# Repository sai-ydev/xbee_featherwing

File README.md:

# xbee_featherwing
XBee Featherwing

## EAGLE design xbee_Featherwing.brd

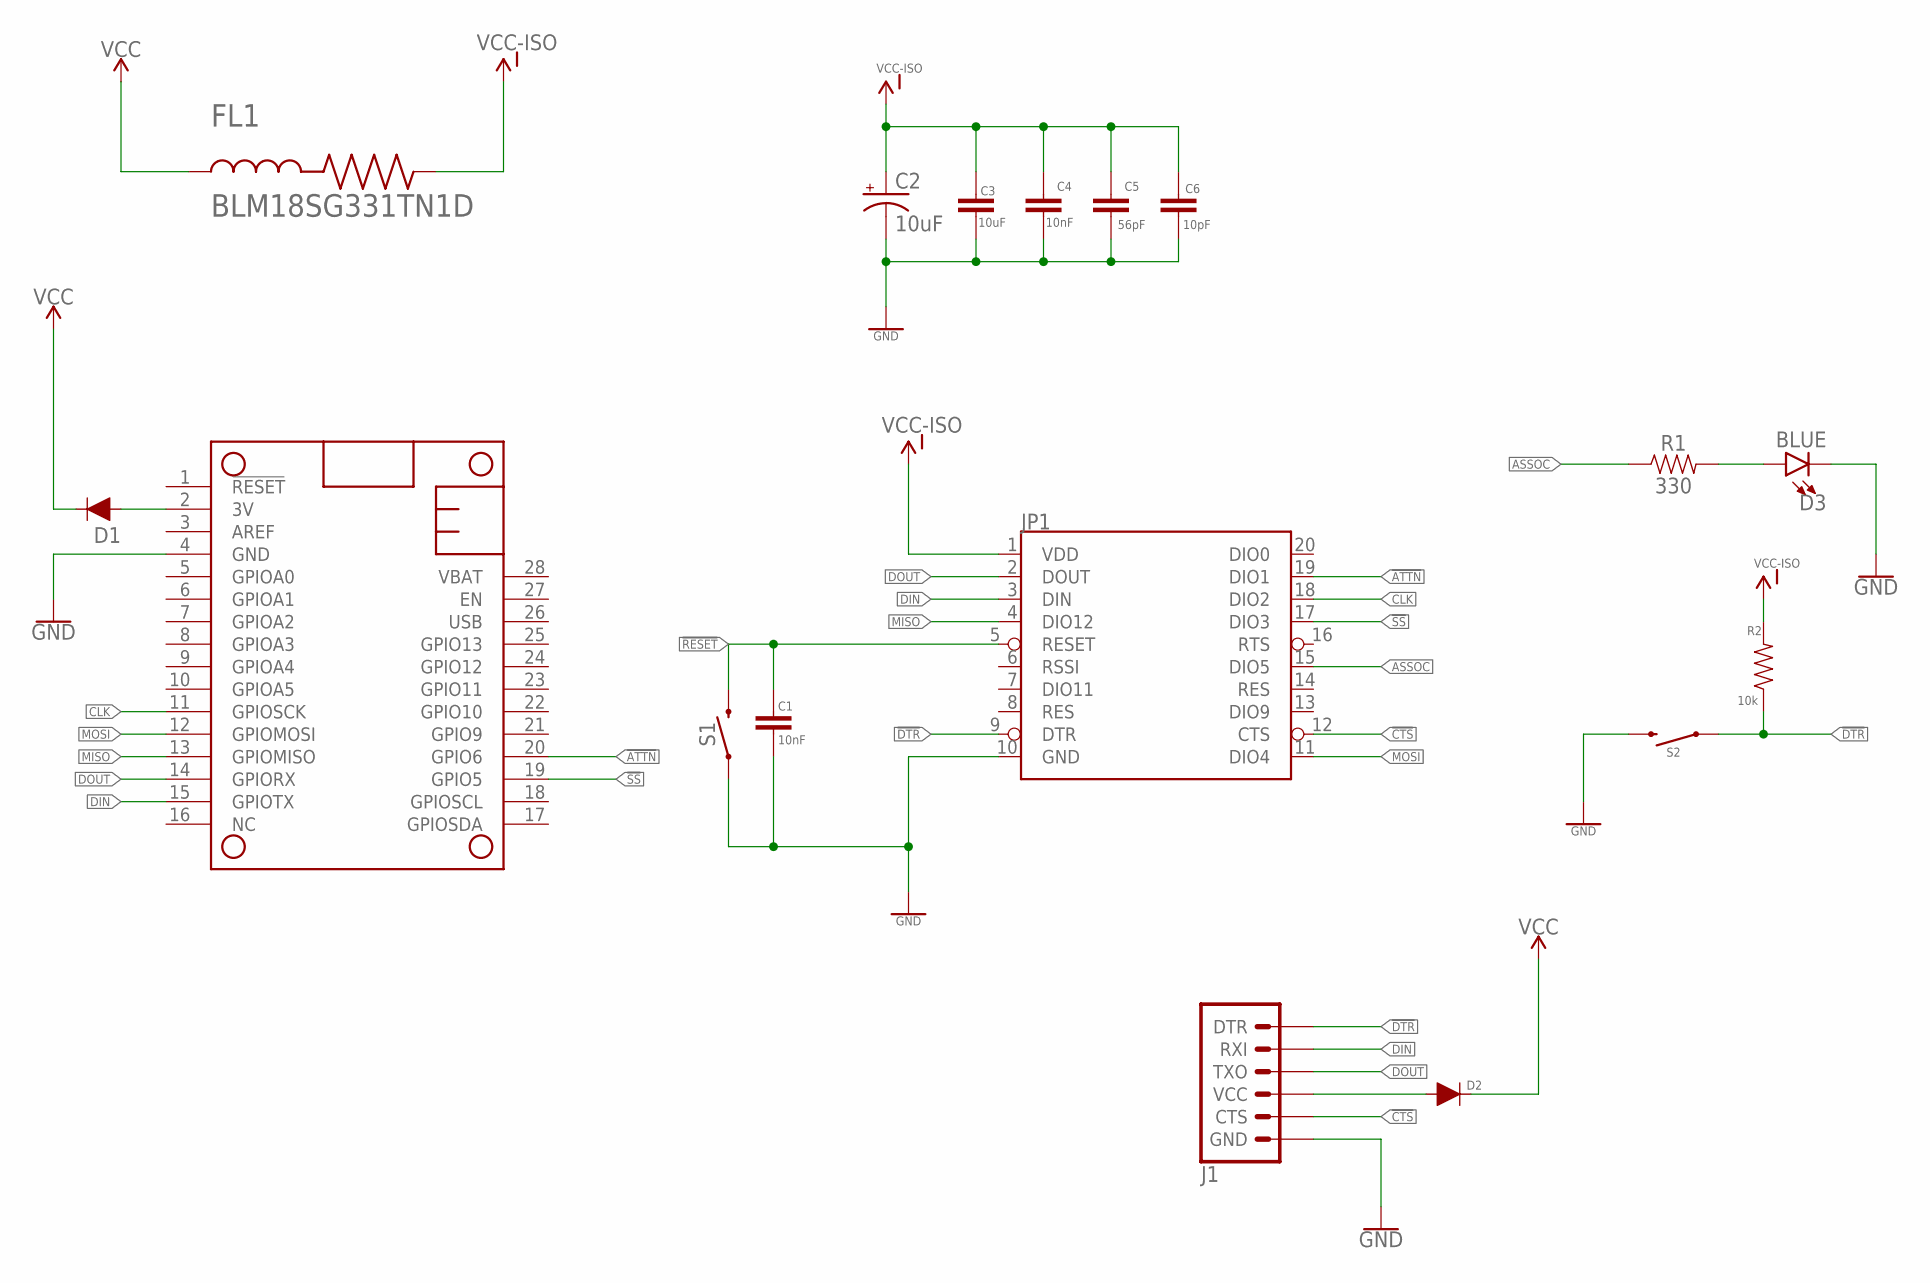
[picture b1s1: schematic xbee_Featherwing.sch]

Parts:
C1, C4: 10nF; 0603
C2: 10uF; EIA3216
C3: 10uF; 0603
C5: 56pF; 0603
C6: 10pF; 0603
D1, D2: 250mA/100V; SOD-323
D3: BLUE; LED-0603
FL1: BLM18SG331TN1D; BEADC1608X65N
J1: 6_PIN_SERIAL_TARGETSILK; 6_PIN_SERIAL_TARGET_SIDE_W_SILK
JP1: XBEESMD; XBEE-SMD
MS1: FEATHERWINGXBEE; FEATHERWING_XBEE
R1: 330; 0603
R2: 10k; 0603
S1, S2: MOMENTARY-SWITCH-SPST-PTH-6.0MM; TACTILE_SWITCH_PTH_6.0MM

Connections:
3V: D1.A, MS1.2 (3V)
!ATTN: JP1.19 (DIO1), MS1.20 (GPIO6)
!CTS: J1.P$5 (CTS), JP1.12 (CTS)
!DTR: J1.P$1 (DTR), JP1.9 (DTR), R2.1, S2.1
!RESET: C1.1, JP1.5 (RESET), S1.3 (2)
!SS: JP1.17 (DIO3), MS1.19 (GPIO5)
ASSOC: JP1.15 (DIO5), R1.1
CLK: JP1.18 (DIO2), MS1.11 (GPIOSCK)
DIN: J1.P$3 (RXI), JP1.3 (DIN), MS1.15 (GPIOTX)
DOUT: J1.P$2 (TXO), JP1.2 (DOUT), MS1.14 (GPIORX)
GND: C1.2, C2.-, C3.2, C4.2, C5.2, C6.2, D3.C, J1.P$6 (GND), JP1.10 (GND), MS1.4 (GND), S1.1, S2.3 (2)
MISO: JP1.4 (DIO12), MS1.13 (GPIOMISO)
MOSI: JP1.11 (DIO4), MS1.12 (GPIOMOSI)
unnamed: D2.A, J1.P$4 (VCC)
unnamed: D3.A, R1.2
VCC: D1.C, D2.C, FL1.1
VCC-ISO: C2.+, C3.1, C4.1, C5.1, C6.1, FL1.2, JP1.1 (VDD), R2.2

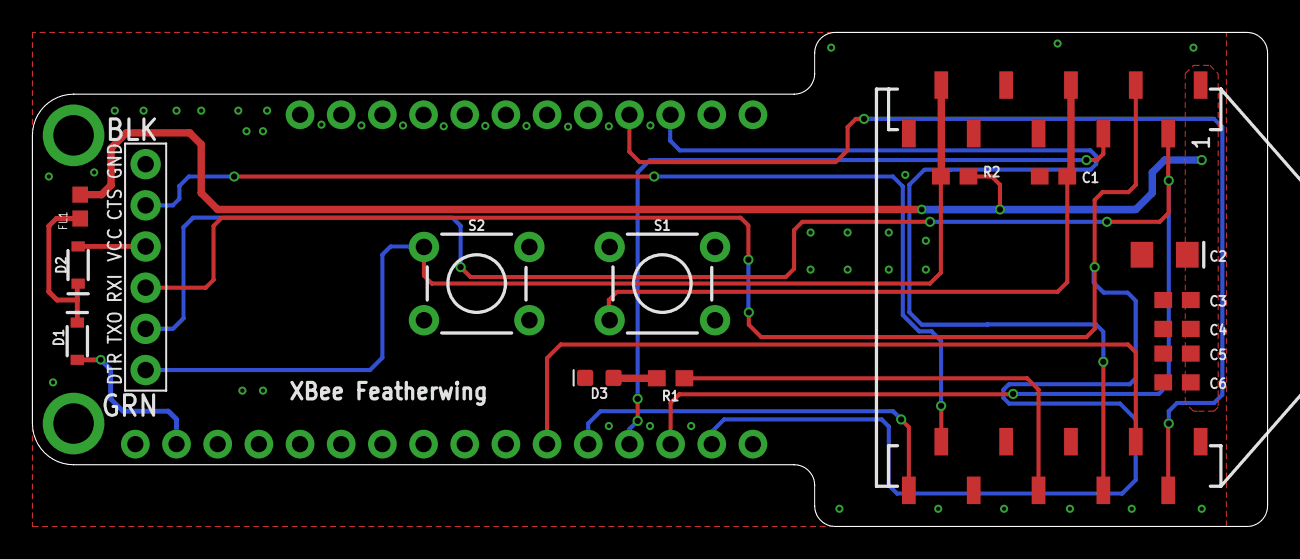
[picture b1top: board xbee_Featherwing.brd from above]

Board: 2 copper layers, 76.2 x 30.5 mm, 17 parts (0 on the bottom side), 17 nets.

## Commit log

2019-12-26 Checking in Xbee Featherwing
    All design files for the xbee featherwing design
2020-01-02 Changing footprint

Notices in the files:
parts and their libraries:
SparkFun-Connectors: Licensing: Creative Commons ShareAlike 4.0 International - https://creativecommons.org/licenses/by-sa/4.0
